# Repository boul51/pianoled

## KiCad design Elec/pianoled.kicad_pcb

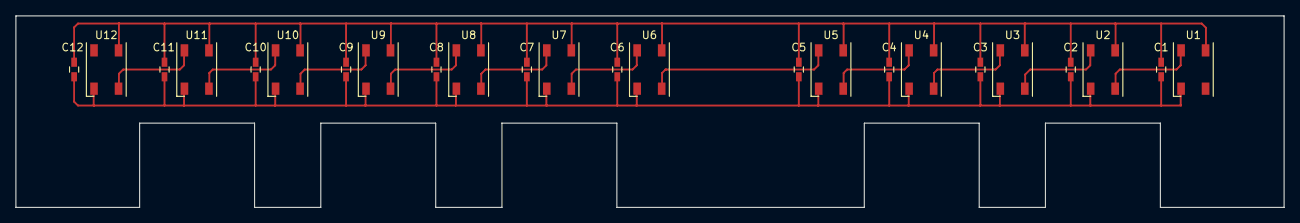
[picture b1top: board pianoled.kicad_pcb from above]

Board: 2 copper layers, 165.6 x 25.0 mm, 24 parts (0 on the bottom side), 13 nets.

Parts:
C1, C2, C3, C4, C5, C6, C7, C8, C9, C10, C11, C12: 100nF; C_0603_HandSoldering
U1, U2, U3, U4, U5, U6, U7, U8, U9, U10, U11, U12: WS8212B; LED_WS2812B-PLCC4

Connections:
/VDD: C1.1, C2.1, C3.1, C4.1, C5.1, C6.1, C7.1, C8.1, C9.1, C10.1, C11.1, C12.1, U1.1, U2.1, U3.1, U4.1, U5.1, U6.1, U7.1, U8.1, U9.1, U10.1, U11.1, U12.1
GND: C1.2, C2.2, C3.2, C4.2, C5.2, C6.2, C7.2, C8.2, C9.2, C10.2, C11.2, C12.2, U1.3, U2.3, U3.3, U4.3, U5.3, U6.3, U7.3, U8.3, U9.3, U10.3, U11.3, U12.3
unnamed: U1.2, U2.4
unnamed: U2.2, U3.4
unnamed: U3.2, U4.4
unnamed: U4.2, U5.4
unnamed: U5.2, U6.4
unnamed: U6.2, U7.4
unnamed: U7.2, U8.4
unnamed: U8.2, U9.4
unnamed: U10.2, U11.4
unnamed: U9.2, U10.4
unnamed: U11.2, U12.4

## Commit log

2016-12-04 Oh siii !
2016-12-04 Added 3D model files and scores files.
2016-12-04 3DModels: Added comments, set default config to print only frame on one octave starting from a C.
2016-12-05 3DModels: Added black keys jitter parameter.
2016-12-05 Kicad: Added kicad files.
2016-12-05 Kicad: Added missing library file.
2016-12-06 3DModels: Added variable jitters for black keys. Small fixes.
2016-12-06 Kicad: removed unused components from eeschema library.
2016-12-06 add .gitignore and initial BOM
2016-12-06 3DModels: Set default depth to 10mm.
2016-12-06 3DModels: Comment out draw_keyboard()
2016-12-06 3DModels: Added PCB footprints (8x10mm)
2016-12-06 3DModels: don't pass unused parameter..
2016-12-06 3DModels: Fixes with footprints positions.
2016-12-07 3DModels: Added reinforcement bars. Set thickness to 1.5, margin to 0.5. Small fixes.
2016-12-07 Added prototypes pictures.
2016-12-07 add .idea to .gitignore
2016-12-07 3DModels: Distinct parameters for x, y and z thickness.
2016-12-07 3DModels: Set default height to 11mm.
2016-12-07 ignore STL/GCODE
2016-12-07 set fp_height to 0.5 (nozzle is 0.4mm)
2016-12-07 Pictures: Added midi keyboard files. Renamed picture files to match tags.
2016-12-07 3DModels: Draw version from contents of version.txt file.
2016-12-08 3DModels: Added vertical part at the back of the frame. Removed horizontal reinforcement bars.
2016-12-16 reduce version text, increase size to allow 3D print, convert Excel to ODS format, add 16.12.2016 gotronic bill
2016-12-16 update ODS
2016-12-18 Arduino: Added sketch (stub containing neopixel and midi initialization)
2016-12-21 add cable guides => structure v1.2
2016-12-21 add borders to the strucutre
2016-12-28 Arduino: Turn on Neopixel LEDs based on MIDI input. Works fine with two LEDs, ttymidi utility and virtual midi keyboard under Linux.
2016-12-30 Arduino: Handle channel colors.
2017-01-09 3DModels: Split pianoled.scad to externalize reusable modules. We'll need this to make assembly tools.
2017-01-09 3DModels: 1st version of black keys tool OK.
2017-01-09 3DModels: Added white key tool.
2017-01-10 Arduino: Update colors every 100ms even if no change occured. Useful when colors are lost by the leds because we touched the wires.
2017-01-10 Test to include only the LED in the black keys tool. Removed unused comment in white keys tool.
2017-01-10 enlarge holes, make the design printable
2017-03-02 update structure with more height (to be able to put the LEDs facing down)
2017-03-18 update structure to work with LED strip and light guides
2017-06-12 update 3Dmodel to version 2.1 => adjust light guides, add drawer-like function on top to slide the LED strip
